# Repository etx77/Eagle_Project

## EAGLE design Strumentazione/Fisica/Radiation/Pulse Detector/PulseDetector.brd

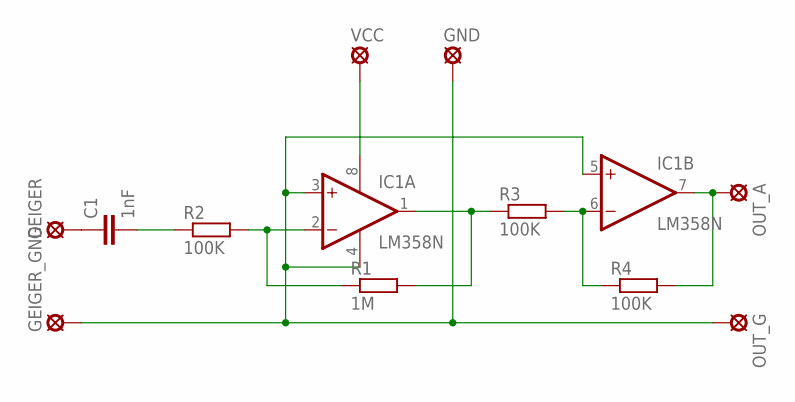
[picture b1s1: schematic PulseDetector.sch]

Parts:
C1: 1nF; C025-025X050
GEIGER: LSP10
GEIGER_GND: LSP10
GND: LSP10
IC1: LM358N; DIL08
OUT_A: LSP10
OUT_G: LSP10
R1: 1M; 0207/10
R2, R3, R4: 100K; 0207/10
VCC: LSP10

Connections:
unnamed: IC1.2 (-IN), R1.1, R2.2
unnamed: GEIGER_GND.MP, GND.MP, IC1.3 (+IN), IC1.4 (V-), IC1.5 (+IN), OUT_G.MP
unnamed: IC1.1 (OUT), R1.2, R3.1
unnamed: IC1.6 (-IN), R3.2, R4.1
unnamed: C1.2, R2.1
unnamed: IC1.8 (V+), VCC.MP
unnamed: IC1.7 (OUT), OUT_A.MP, R4.2
unnamed: C1.1, GEIGER.MP

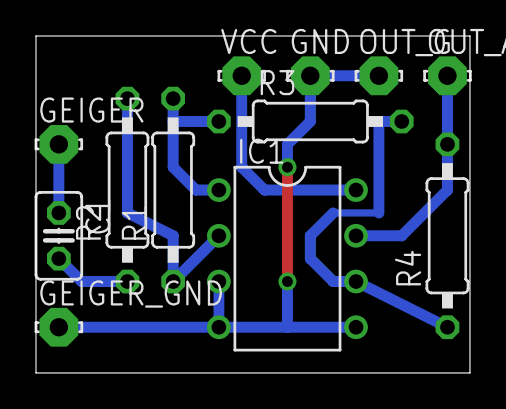
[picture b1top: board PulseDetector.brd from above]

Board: 2 copper layers, 24.1 x 18.7 mm, 12 parts (0 on the bottom side), 8 nets.

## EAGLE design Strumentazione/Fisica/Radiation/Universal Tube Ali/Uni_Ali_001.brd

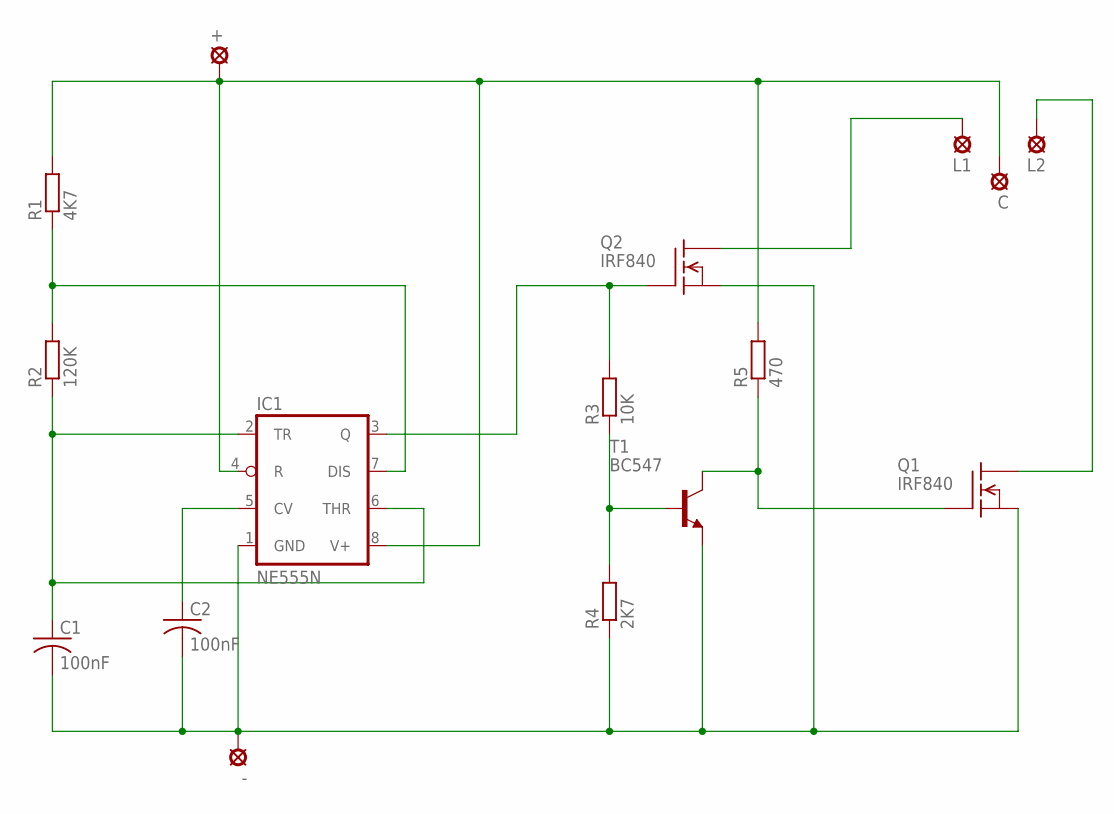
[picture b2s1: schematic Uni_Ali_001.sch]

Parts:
+: LSP10
-: LSP10
C: LSP10
C1, C2: 100nF; C025-024X044
IC1: NE555N; DIL08
L1, L2: LSP10
Q1, Q2: IRF840; TO220
R1: 4K7; 0204/7
R2: 120K; 0204/7
R3: 10K; 0204/7
R4: 2K7; 0204/7
R5: 470; 0204/7
T1: BC547; TO92

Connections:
unnamed: L2.MP, Q1.2 (D)
unnamed: L1.MP, Q2.2 (D)
unnamed: IC1.7 (DIS), R1.1, R2.2
unnamed: C1.1, IC1.2 (TR), IC1.6 (THR), R2.1
unnamed: R3.1, R4.2, T1.2 (B)
unnamed: Q1.1 (G), R5.1, T1.3 (C)
unnamed: -.MP, C1.2, C2.2, IC1.1 (GND), Q1.3 (S), Q2.3 (S), R4.1, T1.1 (E)
unnamed: C2.1, IC1.5 (CV)
unnamed: IC1.3 (Q), Q2.1 (G), R3.2
unnamed: +.MP, C.MP, IC1.4 (R), IC1.8 (V+), R1.2, R5.2

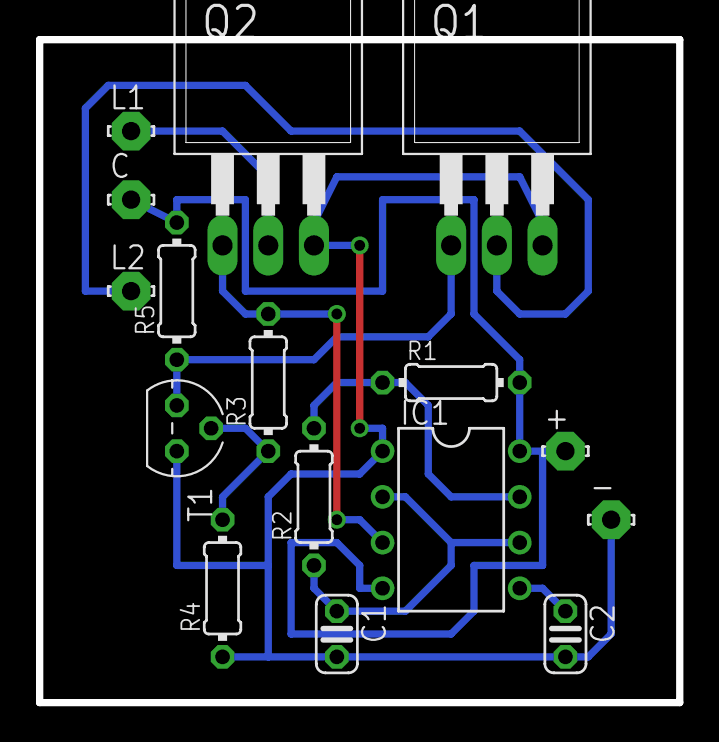
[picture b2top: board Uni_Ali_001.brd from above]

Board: 2 copper layers, 35.6 x 36.8 mm, 16 parts (0 on the bottom side), 10 nets.

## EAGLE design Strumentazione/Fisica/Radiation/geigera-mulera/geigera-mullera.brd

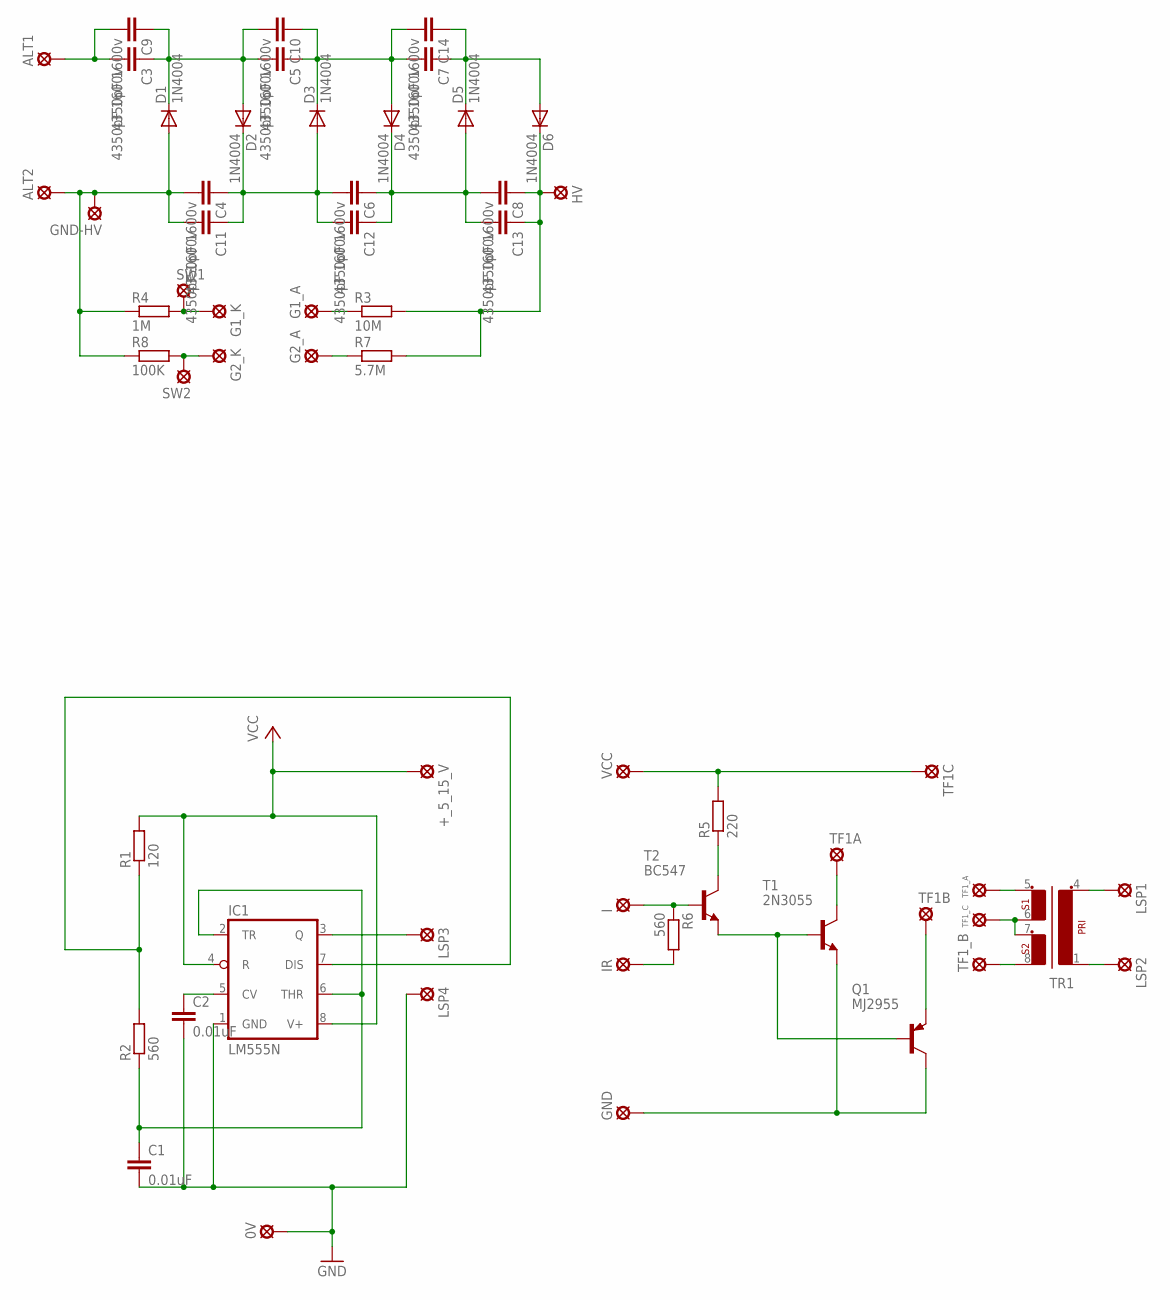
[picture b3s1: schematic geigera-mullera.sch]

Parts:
0V: LSP10
+_5_15_V: LSP10
ALT1, ALT2: LSP10
C1, C2: 0.01uF; C050-024X044
C3, C4, C5, C6, C7, C8, C9, C10, C11, C12, C13, C14: 4350pF 1600v; C225-074X268
D1, D2, D3, D4, D5, D6: 1N4004; DO41-10
G1_A, G1_K, G2_A, G2_K: LSP10
GND: LSP10
GND-HV: LSP10
HV: LSP10
I: LSP10
IC1: LM555N; DIL08-ROUND
IR: LSP10
LSP1, LSP2, LSP3, LSP4: LSP10
Q1: MJ2955; TO3
R1: 120; 0204/7
R2: 560; 0204/7
R3: 10M; 0207/10
R4: 1M; 0207/10
R5: 220; 0207/10
R6: 560; 0207/10
R7: 5.7M; 0207/10
R8: 100K; 0207/10
SW1, SW2: LSP10
T1: 2N3055; TO3
T2: BC547; TO92
TF1A, TF1B, TF1C, TF1_A, TF1_B, TF1_C: LSP10
TR1: EE20-2
VCC: LSP10

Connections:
G2_A: G2_A.MP, R7.1
GND: 0V.MP, C1.2, C2.2, IC1.1 (GND), LSP4.MP
unnamed: C3.1, C5.2, C9.1, C10.2, D1.C, D2.A
unnamed: IC1.7 (DIS), R1.1, R2.2
unnamed: C1.1, IC1.2 (TR), IC1.6 (THR), R2.1
unnamed: TF1_A.MP, TR1.5 (3)
unnamed: R5.2, TF1C.MP, VCC.MP
unnamed: TF1_C.MP, TR1.6 (4), TR1.7 (5)
unnamed: T1.C, T1.C/ (C), TF1A.MP
unnamed: C2.1, IC1.5 (CV)
unnamed: Q1.E, TF1B.MP
unnamed: GND.MP, Q1.C, Q1.C/ (C), T1.E
unnamed: Q1.B, T1.B, T2.1 (E)
unnamed: LSP1.MP, TR1.4 (2)
unnamed: R5.1, T2.3 (C)
unnamed: I.MP, R6.1, T2.2 (B)
unnamed: IR.MP, R6.2
unnamed: LSP2.MP, TR1.1
unnamed: TF1_B.MP, TR1.8 (6)
unnamed: IC1.3 (Q), LSP3.MP
unnamed: ALT1.MP, C3.2, C9.2
unnamed: C4.1, C6.2, C11.1, C12.2, D2.C, D3.A
unnamed: C5.1, C7.2, C10.1, C14.2, D3.C, D4.A
unnamed: C6.1, C8.2, C12.1, C13.2, D4.C, D5.A
unnamed: C7.1, C14.1, D5.C, D6.A
unnamed: C8.1, C13.1, D6.C, HV.MP, R3.2, R7.2
unnamed: ALT2.MP, C4.2, C11.2, D1.A, GND-HV.MP, R4.1, R8.1
unnamed: G1_K.MP, R4.2, SW1.MP
unnamed: G2_K.MP, R8.2, SW2.MP
unnamed: G1_A.MP, R3.1
VCC: +_5_15_V.MP, IC1.4 (R), IC1.8 (V+), R1.2

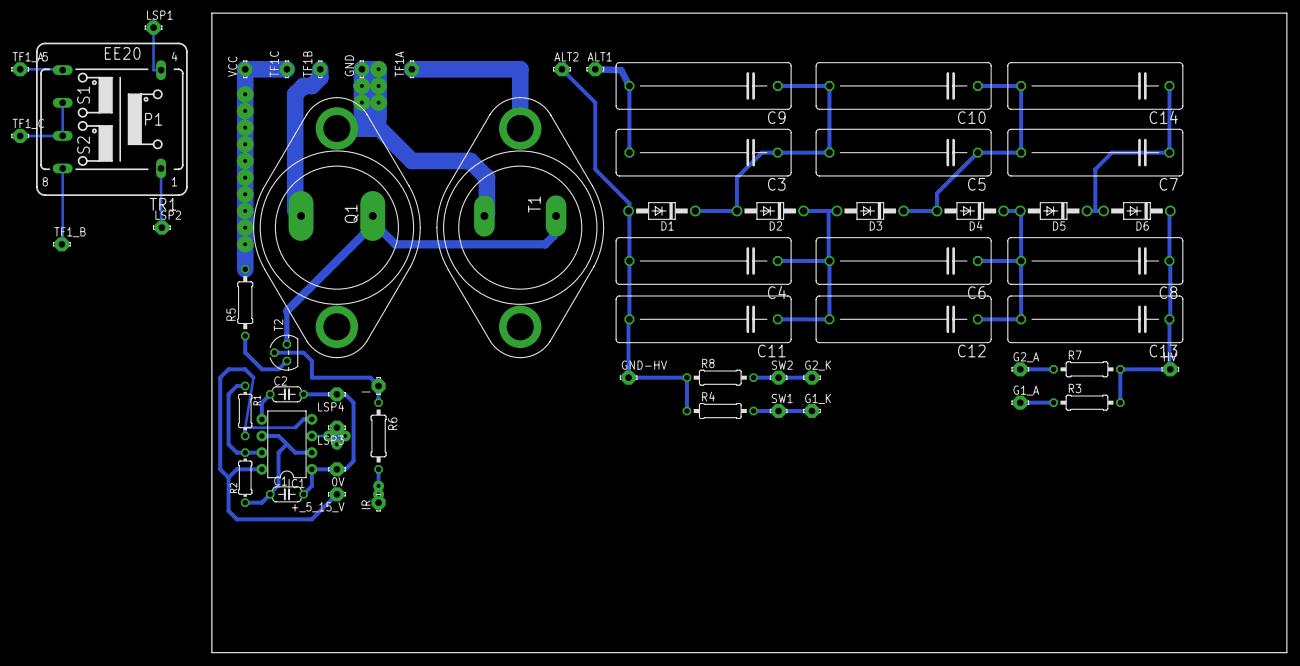
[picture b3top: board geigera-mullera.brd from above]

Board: 2 copper layers, 163.8 x 97.5 mm, 59 parts (0 on the bottom side), 31 nets.

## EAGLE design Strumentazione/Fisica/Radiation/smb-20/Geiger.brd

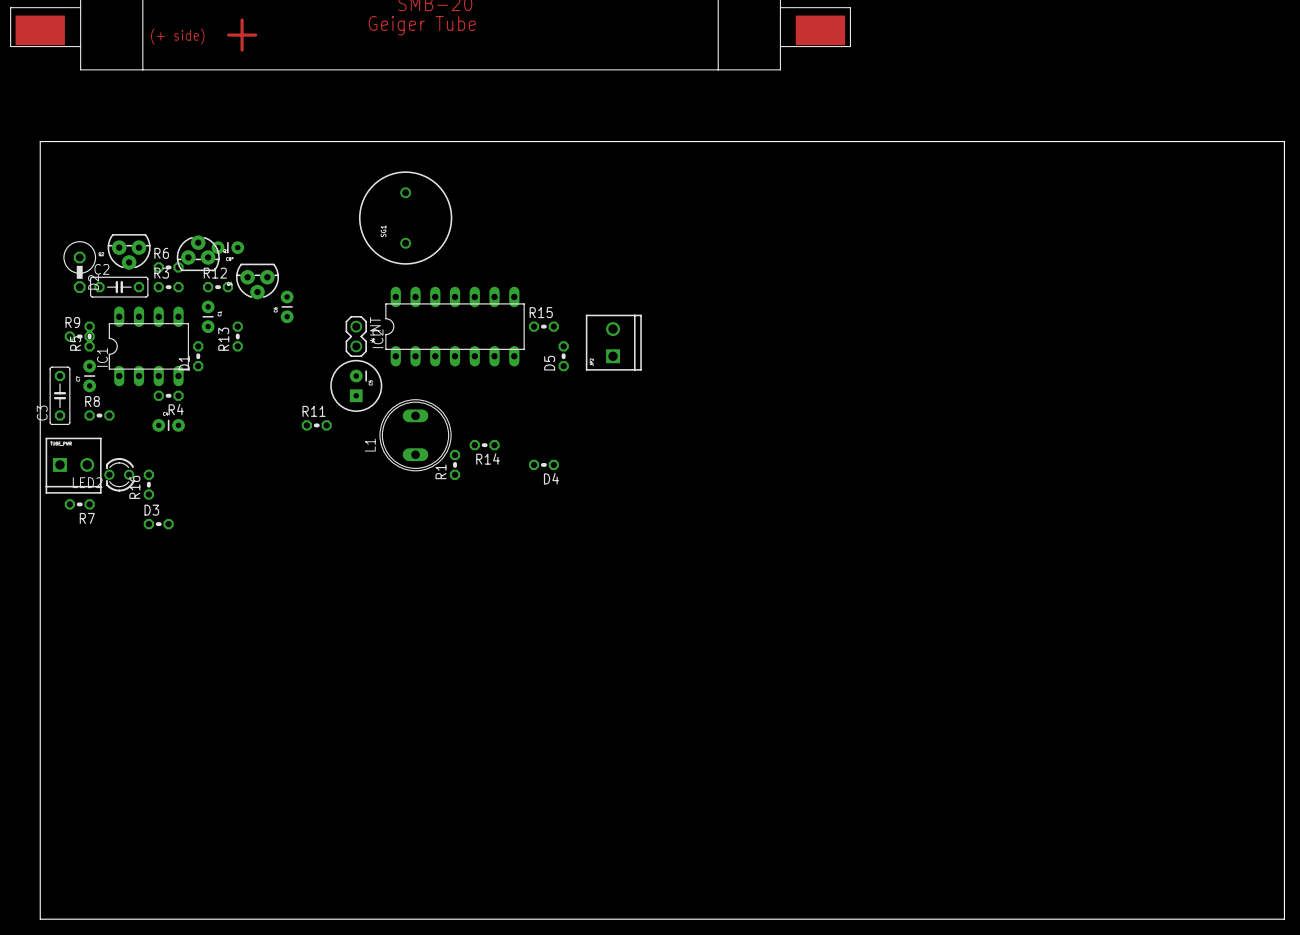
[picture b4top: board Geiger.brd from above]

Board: 2 copper layers, 160.0 x 100.0 mm, 39 parts (0 on the bottom side), 26 nets, no tracks yet.

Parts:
*INT: 1X02
C1: .001uF; CAP-PTH-SMALL
C2, C3: .01uF/600V; C050-025X075
C4: 300pF; CAP-PTH-SMALL
C5: 100uF; CPOL-RADIAL-100UF-25V
C6: .02uF; CAP-PTH-SMALL
C7, C8*: .1uF; CAP-PTH-SMALL
D1, D3, D4, D5: 1N4148; 0204V
D2: 600V_HE_DIODE; VERT_DIODE
GT1: GIEGER_TUBE-SSBM-20; GEIGER_TUBE_SBM-20
IC1: LM555N; DIL08
IC2: 74ACT(HC)14N; DIL14
JP2: SCREWTERMINAL-3.5MM-2
L1: 4.7-10mH; .32IN_RADIAL
LED2: LED3MM
Q1, Q4: 2N2222; TO-92
Q2: MPSA42; TO-92
R1, R5: 100K; 0204V
R3: 220K; 0204V
R4: 330; 0204V
R6: 3.9K; 0204V
R7: 15; 0204V
R8: 1M; 0204V
R9: 4.7M; 0204V
R11, R12, R15: 22K; 0204V
R13: 10K; 0204V
R14: 470K; 0204V
R16: 1.5K; 0204V
SG1: Piezo; BUZZER-12MM
TUBE_PWR: SCREWTERMINAL-3.5MM-2

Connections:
GND: *INT.2, C1.1, C2.2, C3.2, C4.1, C5.2, C6.2, C7.2, IC1.1, IC1.6, IC2.7, JP2.2, LED2.K, Q1.1, Q4.1, R3.1, R7.1, R12.1
unnamed: IC1.3, R4.2, R6.2
unnamed: C2.1, D2.2, R8.2
unnamed: C7.1, D3.1, IC2.1, R14.1
unnamed: C1.2, D1.2, IC1.2, R3.2
unnamed: C4.2, GT1.-, R11.2, TUBE_PWR.2
unnamed: C3.1, R8.1, R9.2
unnamed: GT1.+, R9.1, TUBE_PWR.1
unnamed: Q4.2, R11.1, R12.2
unnamed: D4.2, IC2.2, R16.1
unnamed: IC1.7, Q2.2, R6.1
unnamed: D4.1, D5.1, IC2.3, R1.1
unnamed: IC1.4, Q1.3, R5.1
unnamed: D1.1, R4.1
unnamed: C8*.2, D3.2, Q4.3, R13.1
unnamed: Q1.2, Q2.1, R7.2
unnamed: *INT.1, C8*.1
unnamed: D2.1, L1.2, Q2.3
unnamed: IC2.9, IC2.10
unnamed: D5.2, IC2.6, R15.2
unnamed: C6.1, IC2.5, R15.1
unnamed: IC2.4, IC2.11, IC2.13
unnamed: IC2.12, SG1.-
unnamed: IC2.8, SG1.+
unnamed: LED2.A, R16.2
VCC: C5.1, IC1.8, IC2.14, JP2.1, L1.1, R1.2, R5.2, R13.2, R14.2

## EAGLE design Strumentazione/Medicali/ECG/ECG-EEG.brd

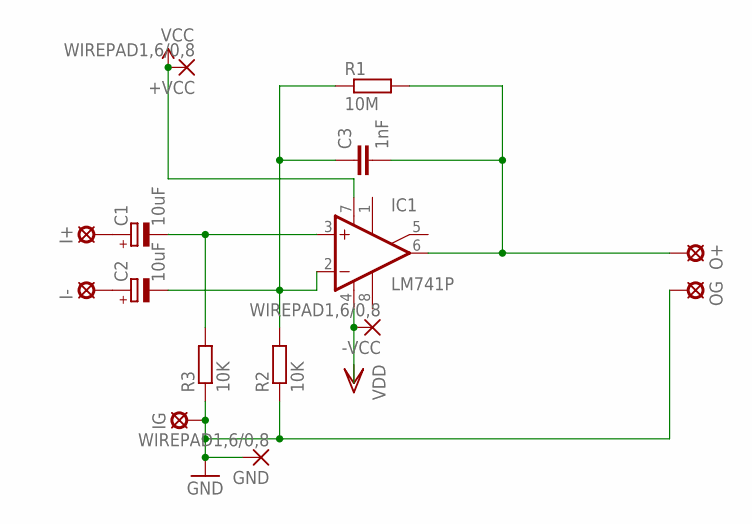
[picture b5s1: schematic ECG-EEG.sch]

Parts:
+VCC: WIREPAD1,6/0,8; 1,6/0,8
-VCC: WIREPAD1,6/0,8; 1,6/0,8
C1, C2: 10uF; E1,8-4
C3: 1nF; C025-025X050
GND: WIREPAD1,6/0,8; 1,6/0,8
I+: LSP10
I-: LSP10
IC1: LM741P; DIL08
IG: LSP10
O+: LSP10
OG: LSP10
R1: 10M; 0204/7
R2, R3: 10K; 0204/7

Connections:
+VCC: +VCC.1, IC1.7 (V+)
GND: GND.1, IG.MP, OG.MP, R2.1, R3.1
unnamed: C1.-, IC1.3 (+IN), R3.2
unnamed: C2.-, C3.1, IC1.2 (-IN), R1.1, R2.2
unnamed: -VCC.1, IC1.4 (V-)
unnamed: C3.2, IC1.6 (OUT), O+.MP, R1.2
unnamed: C1.+, I+.MP
unnamed: C2.+, I-.MP

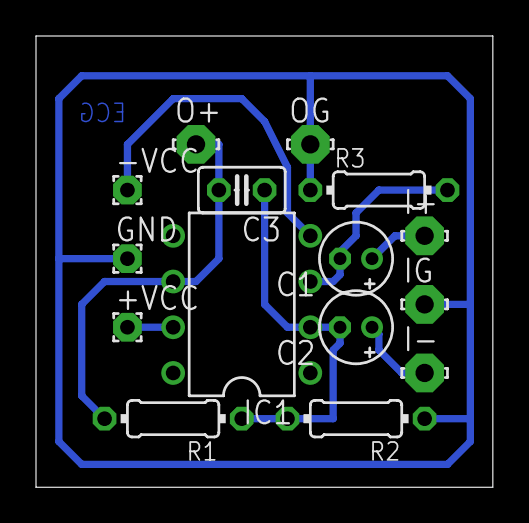
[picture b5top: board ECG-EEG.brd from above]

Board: 2 copper layers, 25.4 x 25.1 mm, 15 parts (0 on the bottom side), 8 nets.

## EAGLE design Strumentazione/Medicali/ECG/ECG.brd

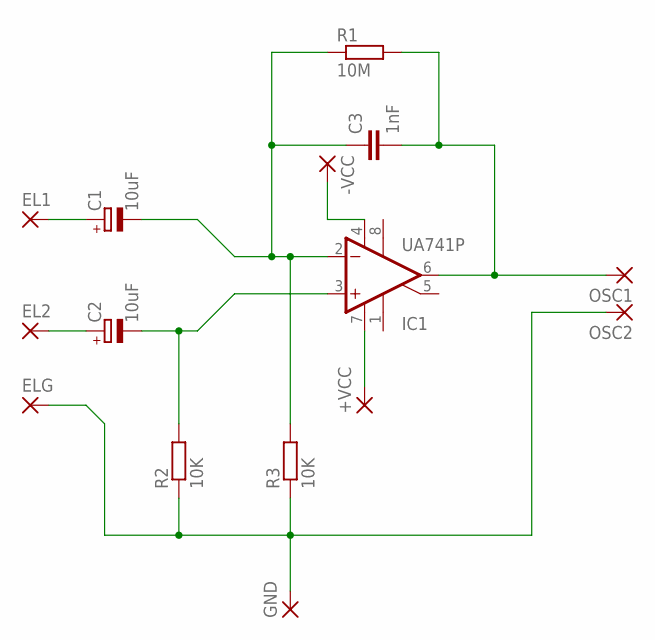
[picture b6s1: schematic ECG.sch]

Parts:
+VCC: 1,6/0,8
-VCC: 1,6/0,8
C1, C2: 10uF; E1,8-4
C3: 1nF; C025-024X044
EL1, EL2: 1,6/0,8
ELG: 1,6/0,8
GND: 1,6/0,8
IC1: UA741P; DIL08
OSC1, OSC2: 1,6/0,8
R1: 10M; 0207/7
R2, R3: 10K; 0207/7

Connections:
unnamed: C1.+, EL1.1
unnamed: C2.-, IC1.3 (+IN), R2.2
unnamed: C1.-, C3.1, IC1.2 (-IN), R1.1, R3.2
unnamed: C3.2, IC1.6 (OUT), OSC1.1, R1.2
unnamed: ELG.1, GND.1, OSC2.1, R2.1, R3.1
unnamed: -VCC.1, IC1.4 (V-)
unnamed: +VCC.1, IC1.7 (V+)
unnamed: C2.+, EL2.1

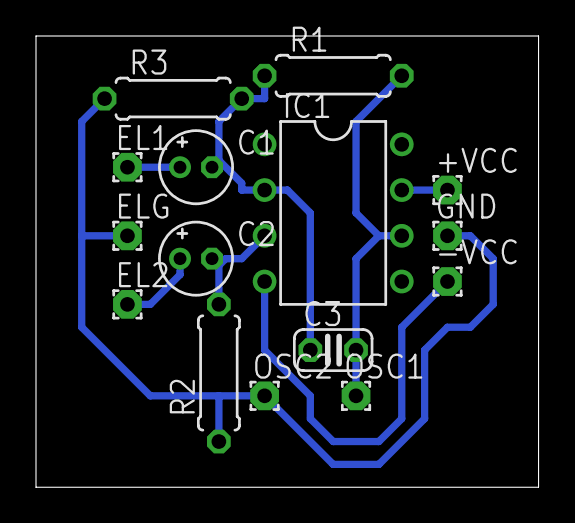
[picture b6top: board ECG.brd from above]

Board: 2 copper layers, 27.9 x 25.1 mm, 15 parts (0 on the bottom side), 8 nets.

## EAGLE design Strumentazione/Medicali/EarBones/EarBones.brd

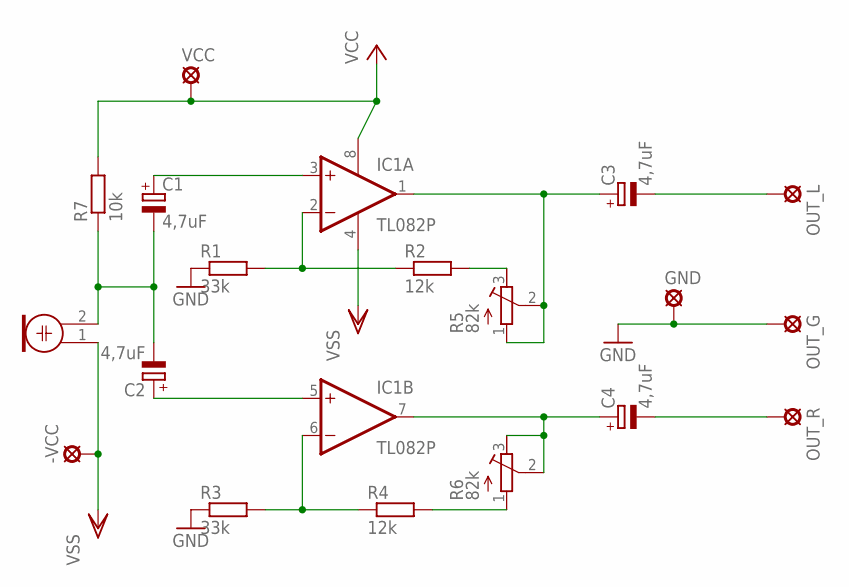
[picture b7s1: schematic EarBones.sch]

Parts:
-VCC: LSP10
C1, C2, C3, C4: 4,7uF; E2,5-6E
GND: LSP10
IC1: TL082P; DIL08
M1: ELECTRET_MICROPHON-WM-61B; WM-61B
OUT_G: LSP10
OUT_L: LSP10
OUT_R: LSP10
R1, R3: 33k; 0207/10
R2, R4: 12k; 0207/10
R5, R6: 82k; RTRIM3339P
R7: 10k; 0207/10
VCC: LSP10

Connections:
GND: GND.MP, OUT_G.MP, R1.1, R3.1
unnamed: IC1.6 (-IN), R3.2, R4.1
unnamed: R4.2, R6.1 (A)
unnamed: C4.+, IC1.7 (OUT), R6.2 (S), R6.3 (E)
unnamed: C3.+, IC1.1 (OUT), R5.1 (A), R5.2 (S)
unnamed: R2.2, R5.3 (E)
unnamed: IC1.2 (-IN), R1.2, R2.1
unnamed: C1.+, IC1.3 (+IN)
unnamed: C2.+, IC1.5 (+IN)
unnamed: C1.-, C2.-, M1.2, R7.1
unnamed: C4.-, OUT_R.MP
unnamed: C3.-, OUT_L.MP
VCC: IC1.8 (V+), R7.2, VCC.MP
VSS: -VCC.MP, IC1.4 (V-), M1.1

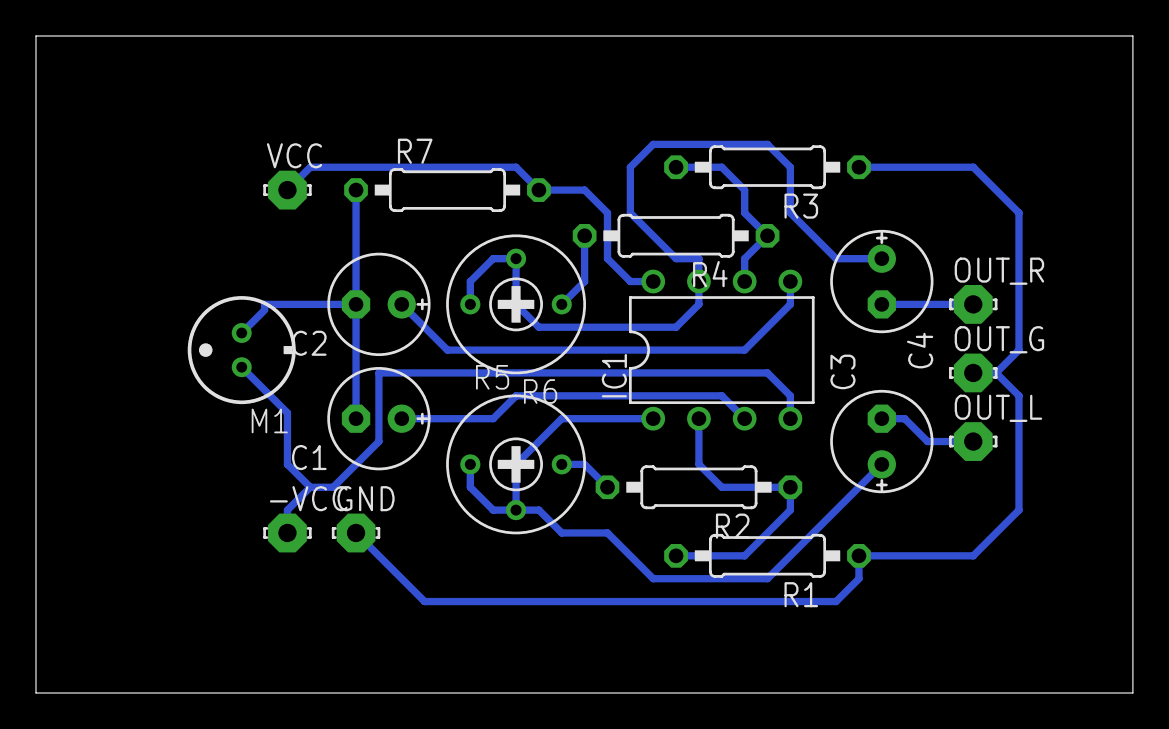
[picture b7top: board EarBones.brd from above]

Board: 2 copper layers, 60.9 x 36.5 mm, 19 parts (0 on the bottom side), 14 nets.

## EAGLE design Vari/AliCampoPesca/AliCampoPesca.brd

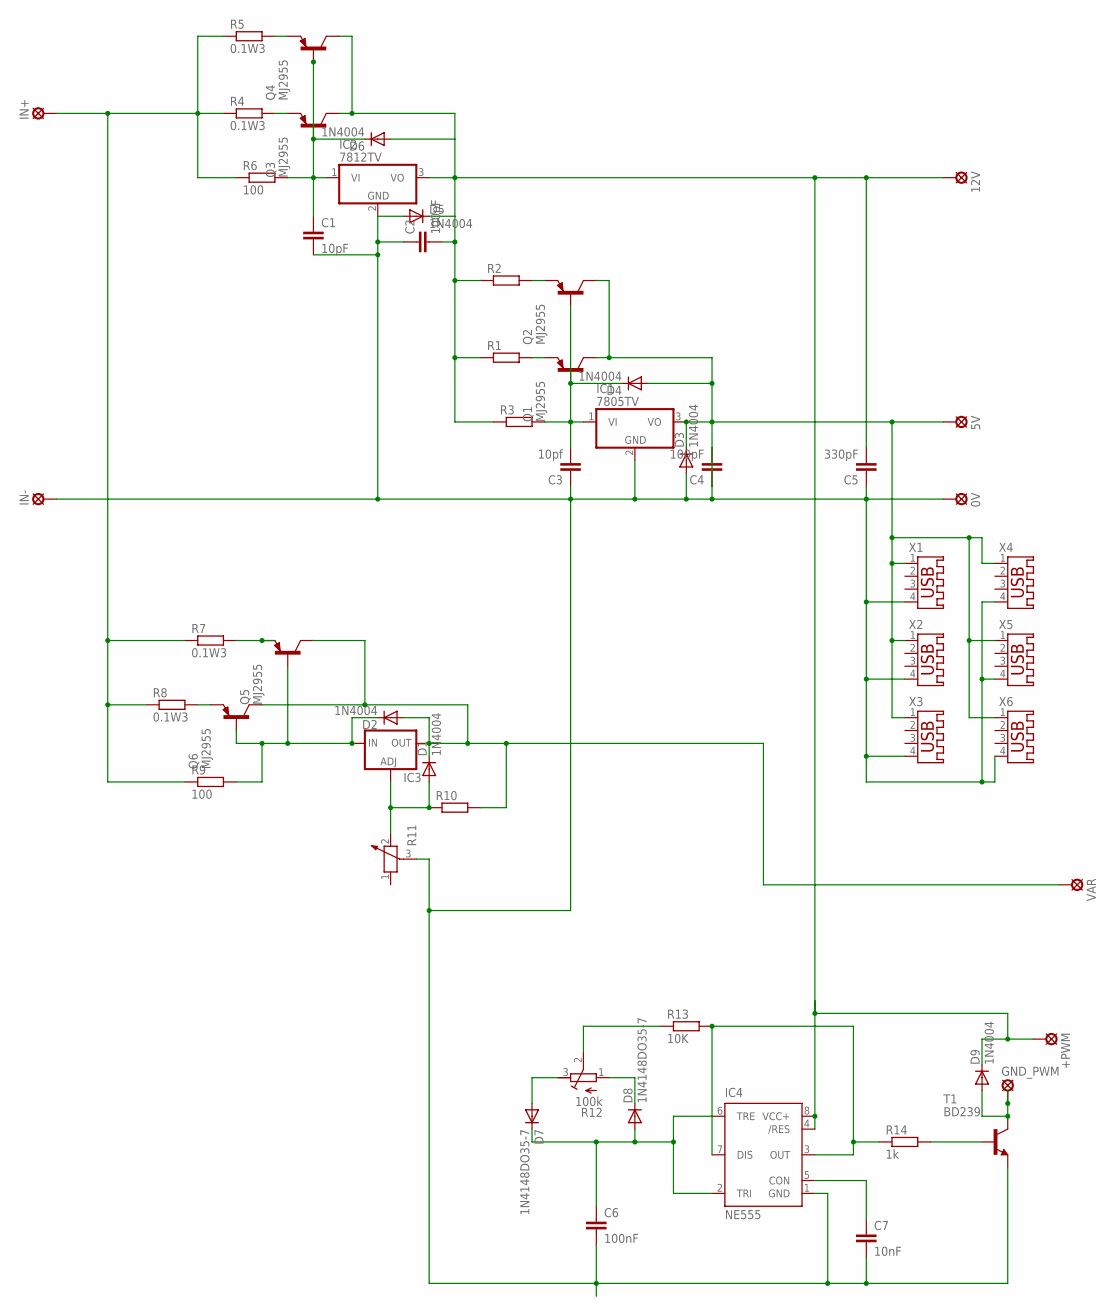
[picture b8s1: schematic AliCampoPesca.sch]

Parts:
0V, 5V, 12V: SE14
+PWM: LSP10
C1: 10pF; C050-024X044
C2, C4: 100pF; C050-024X044
C3: 10pf; C050-024X044
C5: 330pF; C050-024X044
C6: 100nF; C050-024X044
C7: 10nF; C050-024X044
D1, D2, D3, D4, D5, D6, D9: 1N4004; DO41-10
D7, D8: 1N4148DO35-7; DO35-7
GND_PWM: LSP10
IC1: 7805TV; TO220V
IC2: 7812TV; TO220V
IC3: LM317TS; 317TS
IC4: NE555; DIL-08
IN+: SE14
IN-: SE14
Q1, Q2, Q3, Q4, Q5, Q6: MJ2955; TO3
R1, R2, R3: R-EU_0207/15; 0207/15
R4, R5, R7, R8: 0.1W3; 0207/15
R6, R9: 100; 0207/15
R10: R-EU_0207/12; 0207/12
R11: POTENTIOMETER_PT-10; PT-10
R12: 100k; RTRIM3339P
R13: 10K; 0204/7
R14: 1k; 0207/10
T1: BD239; TO220
VAR: SE14
X1, X2, X3, X4, X5, X6: USB-A003

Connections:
unnamed: D2.C, IC3.3 (IN), Q5.B, Q6.B, R9.2
unnamed: D7.A, R12.3 (E)
unnamed: Q1.E, R1.2
unnamed: Q2.E, R2.2
unnamed: C3.2, D4.C, IC1.1 (VI), Q1.B, Q2.B, R3.2
unnamed: D1.A, IC3.1 (ADJ), R10.1, R11.2
unnamed: D1.C, D2.A, IC3.2 (OUT), Q5.C, Q5.C/ (C), Q6.C, Q6.C/ (C), R10.2, VAR.MP
unnamed: IN+.MP, R4.1, R5.1, R6.1, R7.1, R8.1, R9.1
unnamed: Q3.E, R4.2
unnamed: Q4.E, R5.2
unnamed: C1.1, D6.C, IC2.1 (VI), Q3.B, Q4.B, R6.2
unnamed: 0V.MP, 5V.MP, C1.2, C2.1, C3.1, C4.1, C4.2, C5.1, C6.2, C7.2, D3.A, D3.C, D4.A, D5.A, IC1.2 (GND), IC1.3 (VO), IC2.2 (GND), IC4.1 (GND), IN-.MP, Q1.C, Q1.C/ (C), Q2.C, Q2.C/ (C), R11.3, T1.3 (E), X1.1, X1.4, X2.1, X2.4, X3.1, X3.4, X4.1, X4.4, X5.1, X5.4, X6.1, X6.4
unnamed: D8.C, R12.1 (A)
unnamed: Q5.E, R7.2
unnamed: C6.1, D7.C, D8.A, IC4.2 (TRI), IC4.6 (TRE)
unnamed: Q6.E, R8.2
unnamed: C7.1, IC4.5 (CON)
unnamed: 12V.MP, +PWM.MP, C2.2, C5.2, D5.C, D6.A, D9.C, IC2.3 (VO), IC4.4 (/RES), IC4.8 (VCC+), Q3.C, Q3.C/ (C), Q4.C, Q4.C/ (C), R1.1, R2.1, R3.1
unnamed: R12.2 (S), R13.1
unnamed: R14.2, T1.1 (B)
unnamed: D9.A, GND_PWM.MP, T1.2 (C)
unnamed: IC4.3 (OUT), IC4.7 (DIS), R13.2, R14.1

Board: 2 copper layers, 55 parts (0 on the bottom side), 22 nets, no tracks yet.

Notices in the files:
parts and their libraries:
SparkFun-Aesthetics: Licensing: Creative Commons ShareAlike 4.0 International - https://creativecommons.org/licenses/by-sa/4.0
